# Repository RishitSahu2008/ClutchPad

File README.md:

# ClutchPad 
This is a 3*3 macropad that I have built for the hacklub's hackpad project. I plan to use this while gaming. It is my first pcb built hardware project.
## CAD

## PCB and schematics

## What's clutchpad??
Clutchpad is a macropad that is designed to increase your efficiency in tasks and offer a clean, cool look to your setup. It feateures - 
- 9 switches arranged in 3*3 matrix layout
- 6 LED's so you never miss the glow
- an oled display (for funk)
- a rotary encoder for controlling volume
- seed studio's xiao rp2040 microcontroller

And the one major thing it features is customisability. You can change what each key does, how the LED's light up, what to display on the oled screen and even the rotary encoder. 

I made this one for gaming so the keys are assigned accordingly.

## Firmware 
This project uses KMK but i also plan to add QMK later in the future. 
Also curently only one layer is there but i will add further more layers so i can use this for multiple tasks. 

## Challenges faced
I had been out of touch with pcb designing for a long time so it was quite timetaking to realign myself. Also i was new to 3d modelling but it was not too tough to understand. The main thing was the firmware . It took a lot of time as the documentation was not quite undertandable and also there was little content on outube. I tried switching to QMK but found it problematic with the rotary encoder and the display, which the KMK firmware has libraries of. 

## BOM 
- 1x SEED XIAO RP2040
- 1x Rotary encder
- 1x 0.91' OLED display
- 9x mx style switches
- 9x DSA keycaps
- 4x M3 4mm heatset inserts
- 4x M3 16 screws
- Case (2 parts)
- PCB

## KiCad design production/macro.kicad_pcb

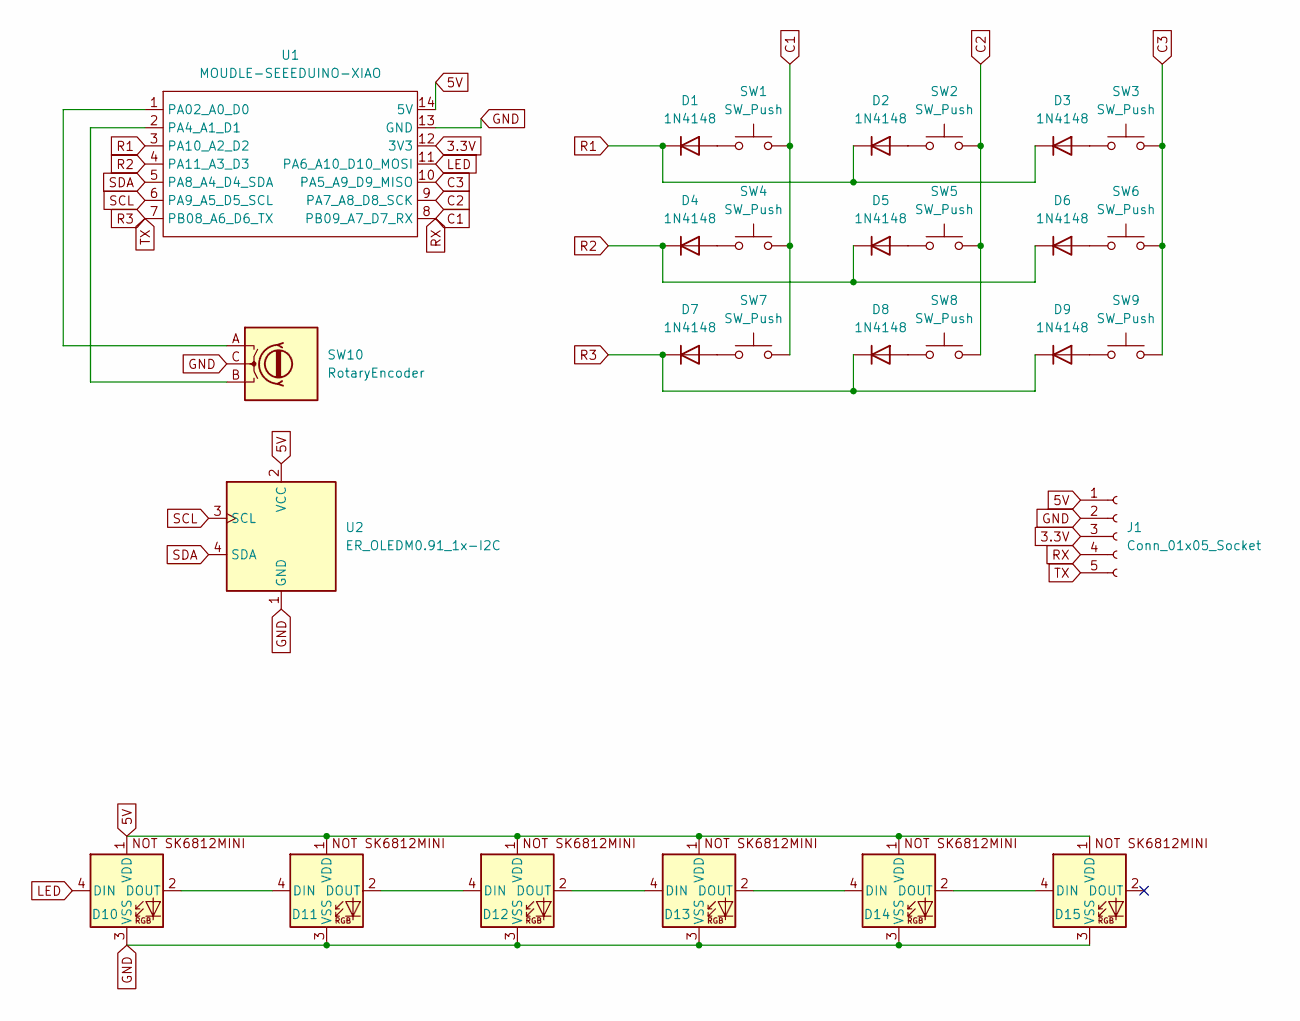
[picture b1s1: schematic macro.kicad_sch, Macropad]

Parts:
D1, D2, D3, D4, D5, D6, D7, D8, D9: 1N4148; D_DO-35_SOD27_P7.62mm_Horizontal
D10, D11, D12, D13, D14, D15: SK6812MINI-E; SK6812MINI-E_fixed
J1: Conn_01x05_Socket; PinSocket_1x05_P2.54mm_Vertical
SW1, SW2, SW3, SW4, SW5, SW6, SW7, SW8, SW9: SW_Push; SW_Cherry_MX_1.00u_PCB
SW10: RotaryEncoder; RotaryEncoder_Alps_EC11E_Vertical_H20mm
U1: MOUDLE-SEEEDUINO-XIAO; XIAO-RP2040-DIP
U2: ER_OLEDM0.91_1x-I2C

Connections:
3.3V: J1.3, U1.12 (3V3)
5V: D10.1 (VDD), D11.1 (VDD), D12.1 (VDD), D13.1 (VDD), D14.1 (VDD), D15.1 (VDD), J1.1, U1.14 (5V), U2.2 (VCC)
C1: J1.4, SW1.2, SW4.2, SW7.2, U1.8 (PB09_A7_D7_RX)
C2: SW2.2, SW5.2, SW8.2, U1.9 (PA7_A8_D8_SCK)
C3: SW3.2, SW6.2, SW9.2, U1.10 (PA5_A9_D9_MISO)
GND: D10.3 (VSS), D11.3 (VSS), D12.3 (VSS), D13.3 (VSS), D14.3 (VSS), D15.3 (VSS), J1.2, SW10.C, U1.13 (GND), U2.1 (GND)
LED: D10.4 (DIN), U1.11 (PA6_A10_D10_MOSI)
unnamed: D1.2 (A), SW1.1
unnamed: D2.2 (A), SW2.1
unnamed: D3.2 (A), SW3.1
unnamed: D4.2 (A), SW4.1
unnamed: D5.2 (A), SW5.1
unnamed: D6.2 (A), SW6.1
unnamed: D7.2 (A), SW7.1
unnamed: D8.2 (A), SW8.1
unnamed: D9.2 (A), SW9.1
unnamed: D10.2 (DOUT), D11.4 (DIN)
unnamed: D11.2 (DOUT), D12.4 (DIN)
unnamed: D12.2 (DOUT), D13.4 (DIN)
unnamed: D13.2 (DOUT), D14.4 (DIN)
unnamed: D14.2 (DOUT), D15.4 (DIN)
unnamed: SW10.A, U1.1 (PA02_A0_D0)
unnamed: SW10.B, U1.2 (PA4_A1_D1)
R1: D1.1 (K), D2.1 (K), D3.1 (K), U1.3 (PA10_A2_D2)
R2: D4.1 (K), D5.1 (K), D6.1 (K), U1.4 (PA11_A3_D3)
R3: D7.1 (K), D8.1 (K), D9.1 (K), J1.5, U1.7 (PB08_A6_D6_TX)
SCL: U1.6 (PA9_A5_D5_SCL), U2.3 (SCL)
SDA: U1.5 (PA8_A4_D4_SDA), U2.4 (SDA)

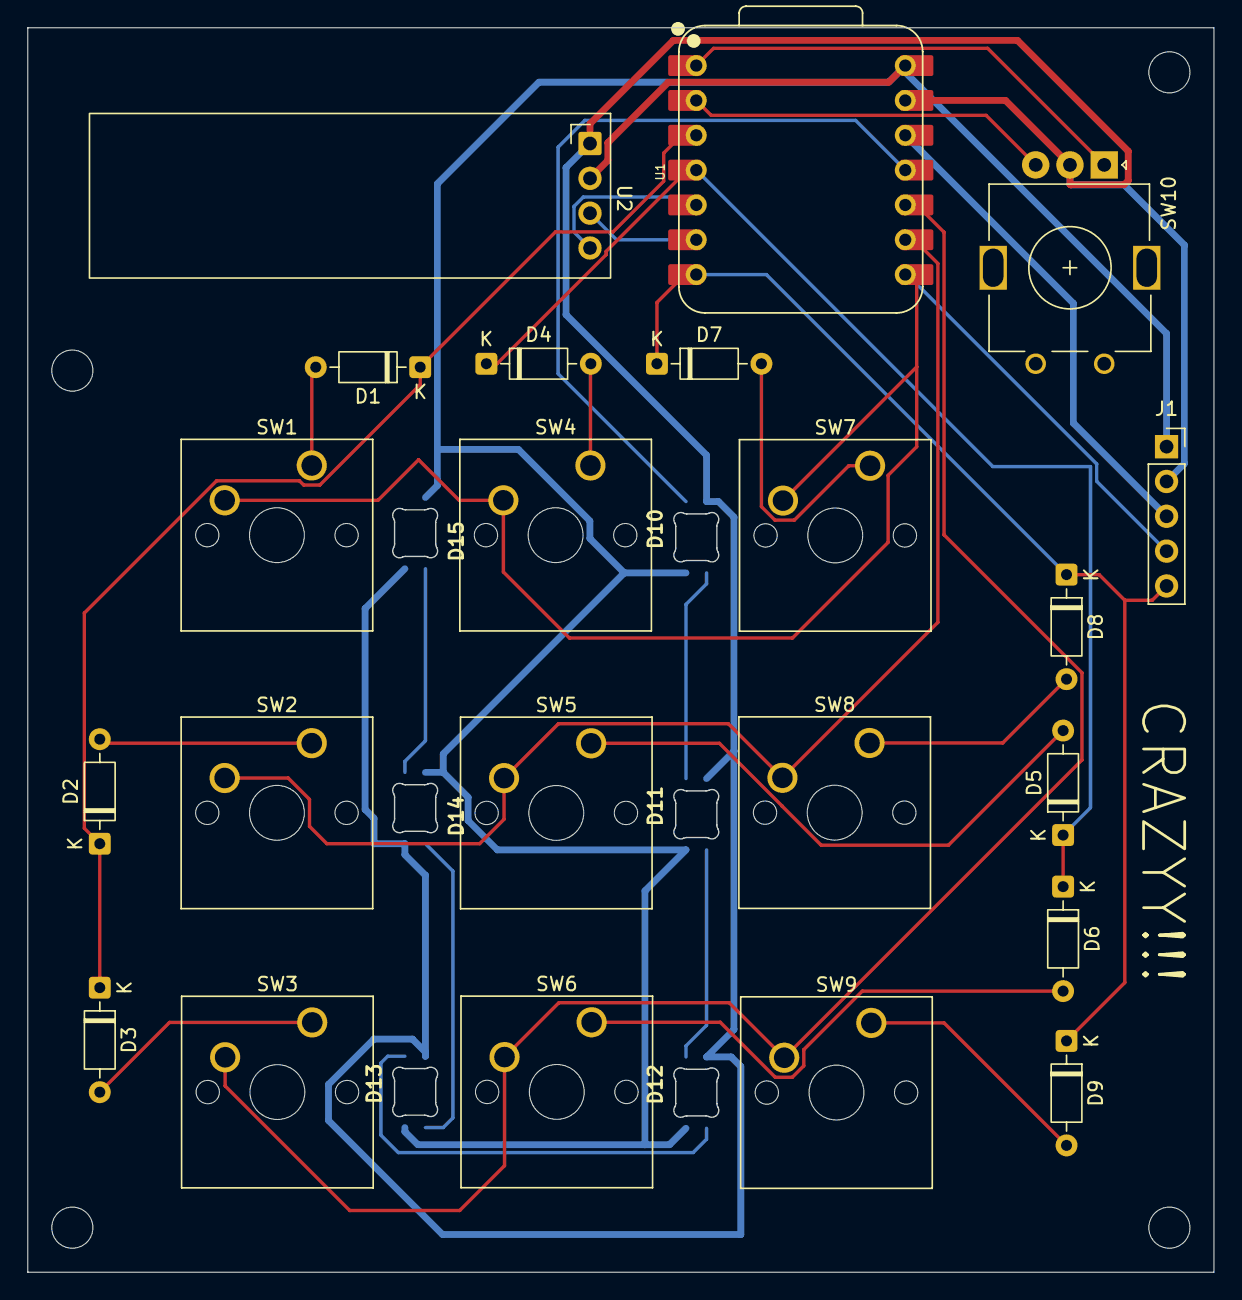
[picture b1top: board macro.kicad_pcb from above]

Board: 2 copper layers, 86.5 x 90.8 mm, 28 parts (0 on the bottom side), 28 nets.
